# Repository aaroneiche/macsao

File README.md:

# Mac SAO 

The Mac SAO is a simple add-on I've built heading into Hackaday Supercon 2024. It is a celebration of the original Macintosh, which debuted 40 years ago in 1984. 

In the spirit of Open source and good faith hardware hacking, all of the code here is open to use. If you do so, I would love to know.

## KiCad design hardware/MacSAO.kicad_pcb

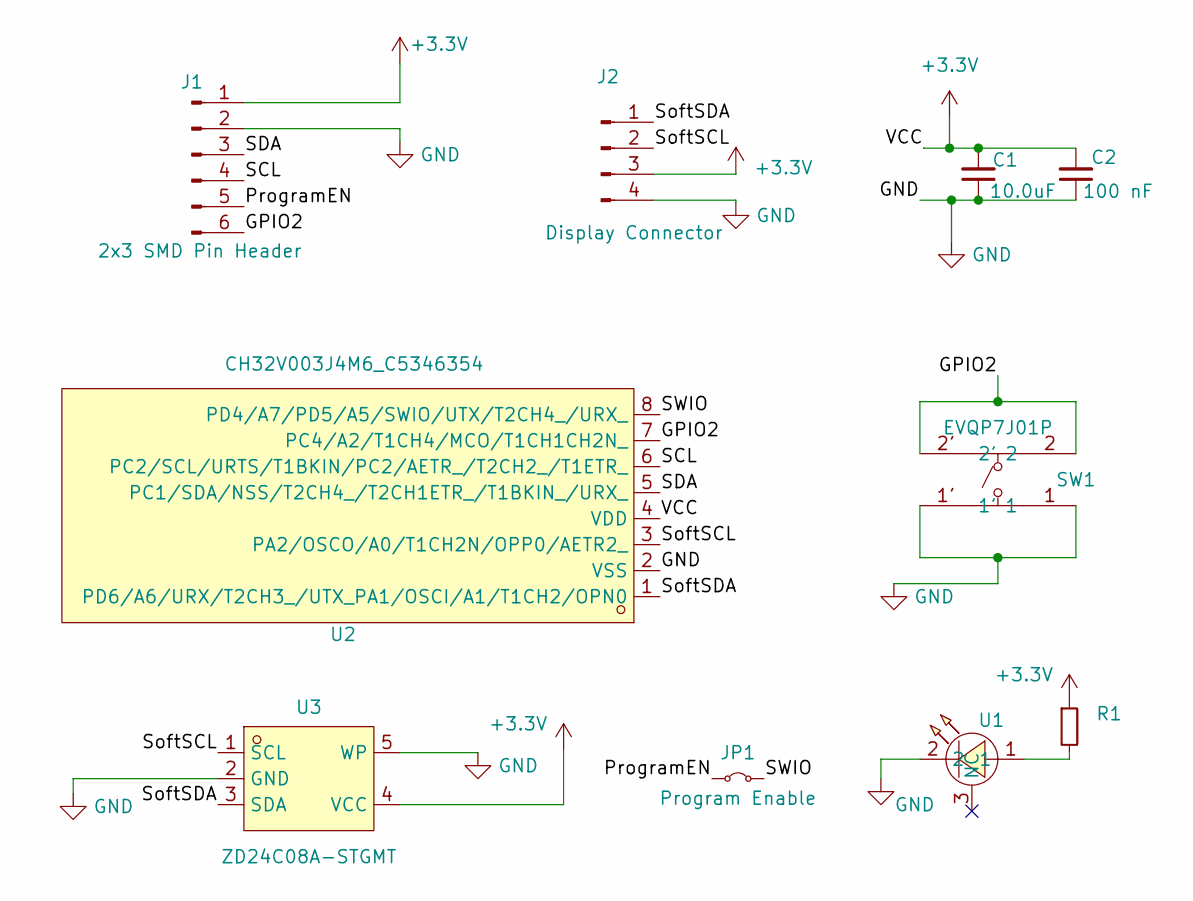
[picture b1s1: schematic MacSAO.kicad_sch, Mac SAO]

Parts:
C1: 10.0uF; C_0805_2012Metric
C2: 100 nF; C_0805_2012Metric
J1: 2x3 SMD Pin Header; PinHeader_2x03_P2.54mm_Vertical_SMD
J2: Display Connector; 1x04_SMD_OLED
JP1: Program Enable; SolderJumper-2_P1.3mm_Bridged_RoundedPad1.0x1.5mm
R1: 1.8Kohm; R_0805_2012Metric
SW1: EVQP7J01P; SW-SMD_EVQP7J01P; LCSC Part C2828254
U1: A-SP110GHC-C01-2C; LED-SMD_L3.0-W1.5_MHS110WDT-C1; LCSC Part C5151480
U2: CH32V003J4M6_C5346354; SOP-8_L4.9-W3.8-P1.27-LS6.0-BL; LCSC Part C5346354
U3: ZD24C08A-STGMT; SOT-23-5_L3.0-W1.7-P0.95-LS2.8-BL; LCSC Part C2896640

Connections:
+3.3V: C1.2, C2.2, J1.1, J2.3, R1.1, U2.4 (VDD), U3.4 (VCC)
/GPIO2: J1.6, SW1.2, SW1.2', U2.7 (PC4/A2/T1CH4/MCO/T1CH1CH2N_)
/ProgramEN: J1.5, JP1.1 (A)
/SCL: J1.4, U2.6 (PC2/SCL/URTS/T1BKIN/PC2/AETR_/T2CH2_/T1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)
/SDA: J1.3, U2.5 (PC1/SDA/NSS/T2CH4_/T2CH1ETR_/T1BKIN_/UR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)
/SWIO: JP1.2 (B), U2.8 (PD4/A7/PD5/A5/SWIO/UTX/T2CH4_/URX_)
/SoftSCL: J2.2, U2.3 (PA2/OSCO/A0/T1CH2N/OPP0/AETR2_), U3.1 (SCL)
/SoftSDA: J2.1, U2.1 (PD6/A6/URX/T2CH3_/UTX_PA1/OSCI/A1/T1CH2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), U3.3 (SDA)
GND: C1.1, C2.1, J1.2, J2.4, SW1.1, SW1.1', U1.2, U2.2 (VSS), U3.2 (GND), U3.5 (WP)
unnamed: R1.2, U1.1

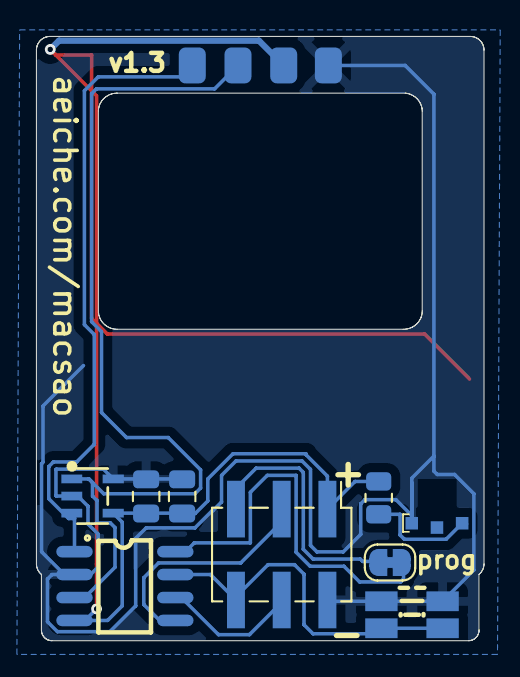
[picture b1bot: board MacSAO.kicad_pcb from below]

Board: 2 copper layers, 24.9 x 33.6 mm, 10 parts (10 on the bottom side), 10 nets.

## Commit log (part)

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2024-10-21 Moves ssd1306 i2c into main Fixes menu selection in mouseToMenu
2024-10-21 Add KiCAD and PCB files
2024-10-21 Add the README
2024-10-27 - Switch decoder commands to decimal - Fixes direct-to-display write - Adds disk icon states arg to desktop - Adds masked disk Icons to tiles -Adds Icon States Tile for bitmap editor
2024-10-28 Adds "LiveDrive" mode
2024-10-29 Moves settings to additional 'mode'.
2024-10-30 Fix EEPROM page boundary write.
2024-10-31 Adds Variable read control byte
    Changes Display write to require offset value.
    Display write no longer appends 255 to end of display.
    Display Stack is now 255 bytes long.
2024-11-02 Fixes window command to include scrollbars Adds "default" animation Fixes background not drawing in LiveDrive when updated
2026-04-19 Updates version 1.3, adds back in detail line
